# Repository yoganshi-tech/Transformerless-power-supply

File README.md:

Transformerless Power Supply – PCB Design (KiCad)

This repository contains the schematic, PCB layout, and 3D board view of a compact transformerless AC-to-DC power supply designed in KiCad 7/8/9.
The circuit uses a capacitive dropper, diode rectifier, Zener regulation, and filtering to provide a stable 5V DC output.

📁 Project Contents

schematic/ – KiCad schematic file (.kicad_sch),
pcb/ – PCB layout file (.kicad_pcb),
gerber/ – Manufacturing-ready Gerber files,
3d_view/ – 3D renders of the completed PCB,
README.md – Project documentation

⚡ Features

Transformerless AC to DC supply,
Capacitive dropper input stage,
Full-bridge rectification using 1N4007 diodes,
Zener-based voltage regulation,
Smoothing using electrolytic capacitors,
On-board 5V output terminal,
Compact single-sided PCB design,
3D model preview included

🛠️ Components Used

Component	  Value / Part Number     	Description
C4	       225J / 2.2µF       	   X2 capacitor for AC dropper
R1	       4.7kΩ	                 Discharge/resistor
D1–D4	     1N4007	                 Bridge rectifier
C1	       0.1µF	                 Noise filter
C2	       1000µF	                Main smoothing capacitor
Zener	     5.1V / 6.2V	          Voltage regulation
C3	       470µF	                Output filter
U1	      Regulator (optional)  	Additional stabilization
J1 / J2	  Screw terminal	        AC input / DC output

🧩 Tools & Software

KiCad 9.0.6 (Schematic + PCB),
3D Viewer inside KiCad,
Any Gerber viewer for fabrication checks

🖼️ Preview
✔️ Schematic
✔️ PCB Layout 
✔️ 3D Render

🏗️ How to Use

Open the project in KiCad.
Review/edit schematic as needed.,
Generate new Gerber files if required:
File → Plot → Gerber,
Upload the Gerbers to any PCB manufacturer (JLCPCB, PCBWay, etc.),
Solder components and test carefully with isolation and safety in mind.

⚠️ Safety Note

This design works directly with AC Mains, which is dangerous.
Use proper insulation, spacing, and testing precautions.
Only attempt this if you understand high-voltage safety.

📜 Author

Designed by Engineer Yoganshi
(PCB, Schematic & Layout)

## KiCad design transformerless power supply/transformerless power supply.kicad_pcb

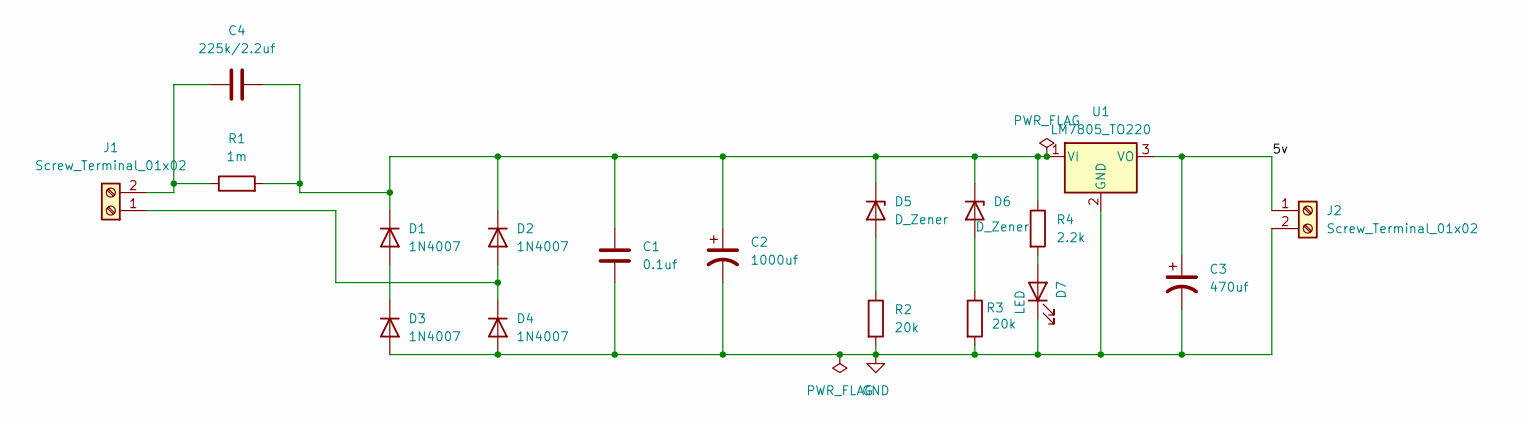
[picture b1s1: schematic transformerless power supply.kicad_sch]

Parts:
C1: 0.1uf; C_Disc_D4.7mm_W2.5mm_P5.00mm
C2: 1000uf; CP_Radial_D10.0mm_P5.00mm
C3: 470uf; CP_Radial_D10.0mm_P3.80mm
C4: 225k/2.2uf; C_Rect_L18.0mm_W6.0mm_P15.00mm_FKS3_FKP3
D1, D2, D3, D4: 1N4007; D_DO-41_SOD81_P10.16mm_Horizontal
D5, D6: D_Zener; D_A-405_P7.62mm_Horizontal
D7: LED; LED_D5.0mm
J1, J2: Screw_Terminal_01x02; TerminalBlock_MaiXu_MX126-5.0-02P_1x02_P5.00mm
R1: 1m; R_Axial_DIN0207_L6.3mm_D2.5mm_P7.62mm_Horizontal
R2, R3: 20k; R_Axial_DIN0207_L6.3mm_D2.5mm_P7.62mm_Horizontal
R4: 2.2k; R_Axial_DIN0207_L6.3mm_D2.5mm_P7.62mm_Horizontal
U1: LM7805_TO220; TO-220-3_Vertical

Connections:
/5v: C3.1, J2.1, U1.3 (VO)
GND: C1.2, C2.2, C3.2, D3.2 (A), D4.2 (A), D7.1 (K), J2.2, R2.2, R3.2, U1.2 (GND)
unnamed: D1.2 (A), D3.1 (K)
unnamed: C1.1, C2.1, C4.1, D1.1 (K), D2.1 (K), D5.1 (K), D6.1 (K), R1.2, R4.1, U1.1 (VI)
unnamed: D2.2 (A), D4.1 (K), J1.1
unnamed: D5.2 (A), R2.1
unnamed: D6.2 (A), R3.1
unnamed: D7.2 (A), R4.2
unnamed: C4.2, J1.2, R1.1

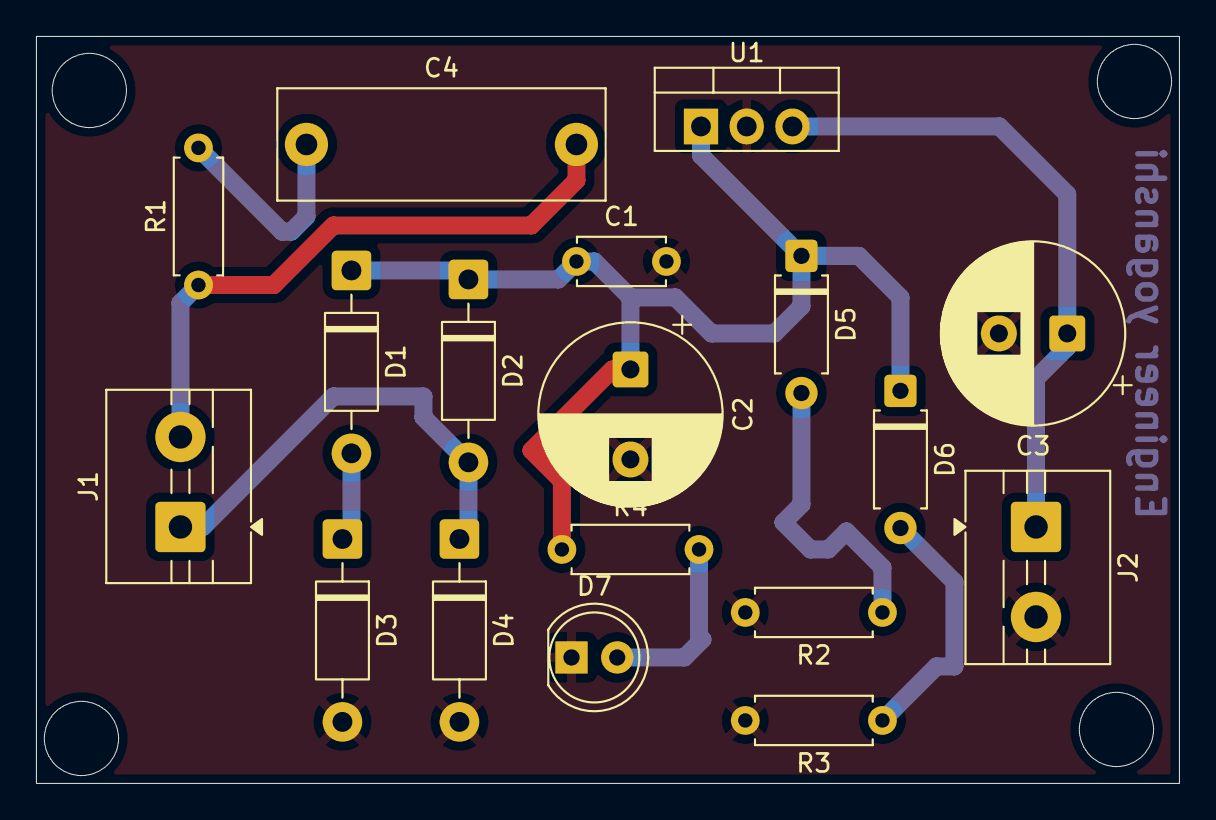
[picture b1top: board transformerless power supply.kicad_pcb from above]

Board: 2 copper layers, 63.5 x 41.5 mm, 18 parts (0 on the bottom side), 9 nets.

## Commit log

2025-12-07 Add README for transformerless power supply project
    This README provides detailed information about a transformerless power supply project, including features, components used, tools, and safety notes.
2025-12-07 Revise README.md for improved content clarity
    Updated project contents and features sections for clarity and consistency. Added additional tools and software information.
